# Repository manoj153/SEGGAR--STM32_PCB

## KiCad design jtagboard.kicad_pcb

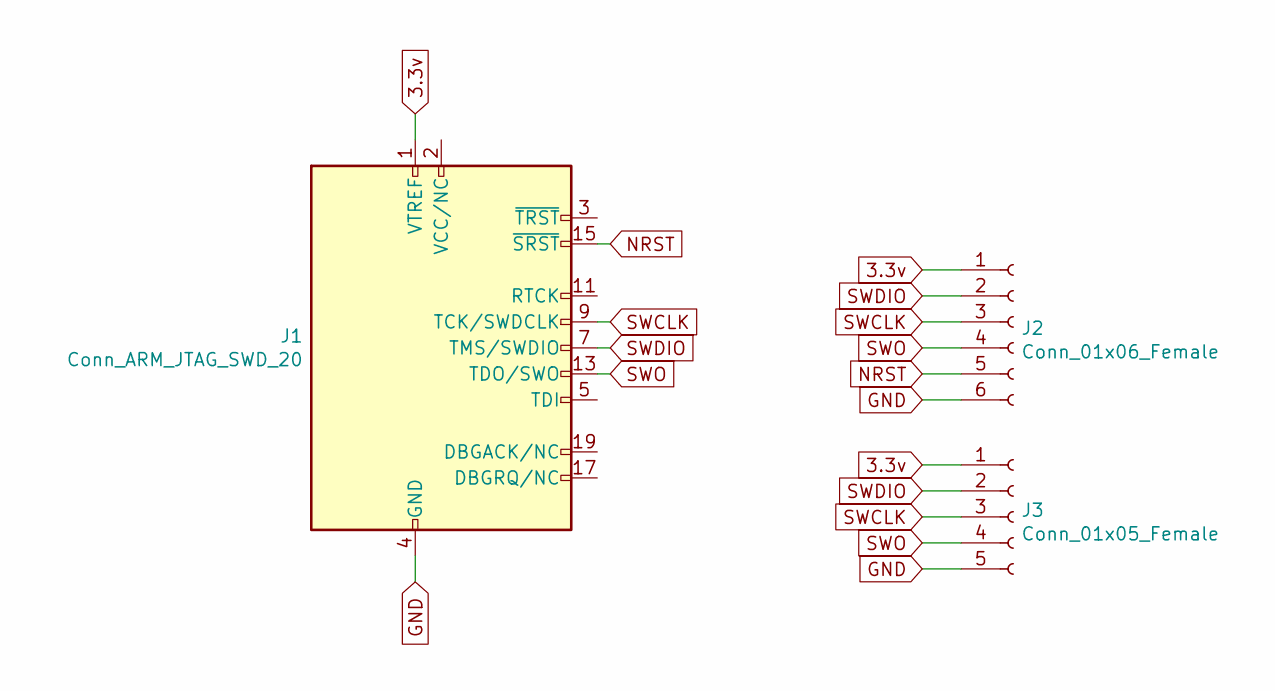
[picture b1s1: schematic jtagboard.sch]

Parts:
J1: Conn_ARM_JTAG_SWD_20; IDC-Header_2x10_P2.54mm_Vertical
J2: Conn_01x06_Female; PinSocket_1x06_P2.54mm_Vertical
J3: Conn_01x05_Female; PinSocket_1x05_P2.54mm_Vertical

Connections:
3.3v: J1.1 (VTREF), J2.1, J3.1
GND: J1.4 (GND), J1.6 (GND), J1.8 (GND), J1.10 (GND), J1.12 (GND), J1.14 (GND), J1.16 (GND), J1.18 (GND), J1.20 (GND), J2.6, J3.5
NRST: J1.15 (~SRST~), J2.5
SWCLK: J1.9 (TCK/SWDCLK), J2.3, J3.3
SWDIO: J1.7 (TMS/SWDIO), J2.2, J3.2
SWO: J1.13 (TDO/SWO), J2.4, J3.4

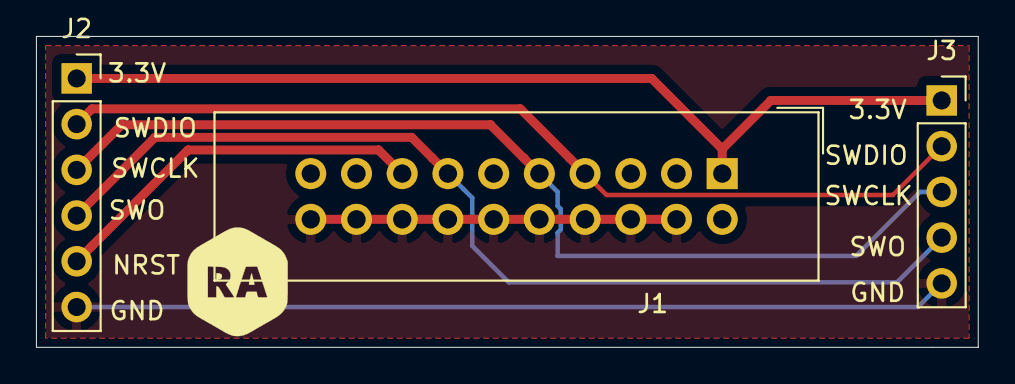
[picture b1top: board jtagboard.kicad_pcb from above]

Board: 2 copper layers, 52.3 x 17.3 mm, 3 parts (0 on the bottom side), 6 nets.
